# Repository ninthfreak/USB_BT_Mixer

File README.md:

# USB_BT_Mixer

A small box with two USB-C inputs and one Bluetooth audio output. Any USB-C host that supports USB audio sees each input as a normal USB sound card. The box mixes both inputs and streams the mix to any Bluetooth audio sink.

- **Architecture (start here): [`docs/architecture.md`](docs/architecture.md)**
- Decision log: [`docs/decisions.md`](docs/decisions.md)
- Design record: [`docs/HANDOFF.md`](docs/HANDOFF.md)
- Corrections since the handoff: [`docs/review-notes.md`](docs/review-notes.md)
- Design envelope (limits and extension points): [`docs/design-envelope.md`](docs/design-envelope.md)
- Viability review: [`docs/viability-review.md`](docs/viability-review.md)
- Parts list: [`hardware/BOM.csv`](hardware/BOM.csv)
- **Latest review (2026-11-16): [`docs/project-review-2026-11.md`](docs/project-review-2026-11.md)**

**Status (2026-11-16): designed, nothing built.**

| Part | State |
|---|---|
| Hardware | Two Waveshare RP2350-USB-C input boards and a Waveshare ESP32-DEV-KIT-WROOM-32E-N4 solder flat onto a carrier PCB ([`hardware/carrier/`](hardware/carrier/)). Routed and DRC clean; **not ordered**. Print [`carrier-fit-check.pdf`](hardware/carrier/carrier-fit-check.pdf) and lay the real boards on it first |
| Firmware | Not started. Design: [`docs/architecture.md`](docs/architecture.md) |
| Enclosure | The modelled box is for the earlier hand-wired build and is out of date. The carrier needs a new one |

Each input board's native USB port faces its host through the enclosure wall and reaches the shared rail through its own Schottky. The ESP32 mixes, owns the audio clock and is the Bluetooth A2DP source. Configured from any browser via a page the box serves over USB; no case buttons. See [`docs/decisions.md`](docs/decisions.md).

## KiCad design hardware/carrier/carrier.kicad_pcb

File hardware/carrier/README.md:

# Carrier board

> **Status: KiCad DRC clean, routed, not built, not ordered.**
>
> - **Re-laid 2026-11-16.** The input boards' land pattern had been the
>   mirror image of the real board since it was first drawn. It is corrected,
>   and the build now holds the placed board against Waveshare's own pictures
>   ([`docs/project-review-2026-11.md`](../../docs/project-review-2026-11.md) #1).
> - **Before ordering, print [`carrier-fit-check.pdf`](carrier-fit-check.pdf)
>   at 100 % and lay the three real modules on it.** Every land is named; the
>   names must match the labels on the modules.
> - **Antenna clearance: accepted as is** (owner, 2026-10-26). Copper is
>   6.55 mm in front of the antenna against Espressif's 15 mm; the antenna
>   itself hangs fully past the board edge
>   ([`AUDIT.md` #21](AUDIT.md#21-antenna-clearance-on-the-front-side-new)).
> - Recommendation before ordering: **the two-I2S clock loop-back is still
>   untested.** A jumper-wire bench test of one input board + the ESP32 would
>   prove it for the price of an afternoon.

One flat PCB that the three modules solder onto, replacing the hand-wired
loom. All passives are through-hole and live on it.

## At a glance

| | |
|---|---|
| Size | 70.0 × 79.6 mm, L-shaped (see below), 2 layers, 1.6 mm |
| Parts | U1, U2 input boards; U3 ESP32 devkit; 2 Schottky diodes; 8 resistors, all 1 kΩ (R1–R6 standing, R10/R11 lying); 1 capacitor; two 2-pin debug headers; 2 test pads |
| Nets | 20: 16 signal, 3 power (VBUS1, VBUS2, RAIL), GND |
| Rules | 0.40 mm track, 0.25 mm clearance, 0.8/0.4 mm vias, 0.5 mm copper to edge, 0.5 mm drill to drill. Loose for any fab |
| Top layer | **Every signal.** No signal changes layer: 0 signal vias |
| Bottom layer | Ground plane (91 % of the board) plus the rail only |
| Routing | Freerouting: 81 signal segments; the rail, ground stubs and three short links by hand; 568 mm of track; 5 vias, all ground |
| Joints to solder | 36 of 70 module lands, plus the passives |

## How the board is laid out

The rules, so it reads the way it works (owner, 2026-10-27):

- **Top layer: signals.** Every signal stays on top from end to end.
- **Bottom layer: ground and power.** A solid ground plane. The rail is the
  only track on it: from input 2's diode across the front, **in front of
  input 1's ground pad**, then down the left edge to the ESP32's 5V pad. No
  signal runs along it, and every module's ground via lands in the one main
  plane (review #2).
- **Related lines run together.** Each board's I2S lines and its UART pair
  travel as groups.

Each module lies exactly as in its picture in `docs/sources/`:

| Module | As placed | Picture |
|---|---|---|
| Input boards | **Native USB port at the front**, hanging 1 mm past the edge. 5V is the front-left pad. Power and I2S run down the **left** edge, UART and debug down the **right**. The PIO-USB port faces inward, unused | `rp2350-usb-c-pinout.png` |
| ESP32 | USB-C end 1 mm past the **left** edge, antenna past the notch on the **right**. The row facing the input boards is J3: 5V at the left … 3V3 at the antenna end | `esp32-dev-kit-drawing.png` |

Seen from the ESP32's front row, west to east:

| ESP32 pin | Carries | Goes to |
|---|---|---|
| IO13 | Input 1 audio | Down the left margin from input 1's left edge |
| IO14, IO26 | LRCK out, BCLK out, through R3 and R1 | Under input 1 to its left edge |
| IO25, IO33 | Input 1's UART (TX through R5, RX) | Up the channel to input 1's right edge |
| IO32, IO35 | BCLK in, LRCK in (the loop-backs), and on through R2 and R4 | To input 2's left edge |
| gaps east of IO35 | Input 2's audio, TX, and RX (through R6) | Under the ESP32 to IO18, IO19, IO21 on its rear row |

The clocks' output pins face input 1 and their loop-back pins face input 2,
so the two links under the ESP32 **nest instead of crossing**, and input 1's
UART ends on the two pads between them. Three lines pass between the pads of
a standing resistor (BCLK to input 1 under R3; input 2's audio under R2 and
R4). That is the only "crossing" on the board, and it is why no signal needs
the bottom layer.

| Where | What |
|---|---|
| Left margin | Input 1's diode D1 and bleed R10 at its 5V pad; the rail (bottom); test points; rail bulk C1 at the ESP32's 5V pad |
| Channel between the boards | Input 2's diode D2 and bleed R11 at its 5V pad; input 1's debug header J1; input 1's UART lanes |
| Strip in front of the ESP32 | R3, R1, R5, R2, R4, R6 standing in a row, each at the pin or gap it serves |
| Right margin | Input 2's debug header J2 |

## Why it is an L, not a rectangle

The front must be 70 mm wide for the two input boards side by side. The ESP32
devkit sits across the back, its USB-C end hanging 1 mm past the left edge so
a flashing cable fits. That puts the antenna at the right.

Espressif's first choice is an antenna **outside** the base board, with any
board under it cut away. So the back-right corner is cut off and the
devkit's antenna end hangs 7.5 mm into free air. An L costs nothing extra:
fabs price by the bounding box.

The catch is the antenna's front side, where the front-right block comes
close: 6.55 mm, where Espressif asks for 15. The owner accepted that rather
than make the board ~8.5 mm deeper ([AUDIT.md #21](AUDIT.md#21-antenna-clearance-on-the-front-side-new)).

## Build

```sh
./build.sh                          # regenerate and check everything
/usr/bin/python3 route.py --reroute # only after moving parts or changing nets
```

Everything runs under the **system** python (`/usr/bin/python3`), which has
KiCad 7's `pcbnew` bindings. Every step must pass.

The build does **not** run Freerouting: its output varies from run to run.
It lays the committed result, `carrier.ses`. If the placement or netlist has
changed since that route was made, `route.py` stops and says to reroute.
Rerouting downloads Freerouting 2.1.0 once (SHA-256 checked, analytics off)
and needs Java 17 or later; it takes a few seconds. Whether a route is
complete is decided by KiCad's connectivity, not by Freerouting's own count.

`carrier.kicad_sch`, `carrier.kicad_pcb`, `carrier.pretty/`,
`CONNECTIONS.md` and the PDFs are generated. Edit `netlist.py` (connectivity),
`gen_pcb.py` (placement) or `route.py` (hand-laid copper) and rebuild. Never
hand-edit the outputs.

## Files

| File | What |
|---|---|
| `netlist.py` | **Single source of truth** for connectivity: parts, pin maps, nets, footprints, and what is deliberately unconnected |
| `gen_fp.py` | The two module land patterns, from `enclosure/boards.scad`, each drawn as its picture |
| `gen_sch.py` | `carrier.kicad_sch` |
| `gen_table.py` | `CONNECTIONS.md`: every net, and which pads to solder |
| `gen_pcb.py` | `carrier.kicad_pcb`, built with pcbnew: outline, placement, pad nets, schematic links, labels, the ground pour |
| `route.py` | Lays the rail, ground stubs and three links by hand, every other signal from `carrier.ses`; `--reroute` runs Freerouting to make a new one |
| `specctra.py` | Design export edits and session import between KiCad and Freerouting |
| `carrier.ses`, `carrier-route.json` | The committed route, and the hash of the design it was made for |
| `drc.py` | **The gate.** KiCad's own DRC with this board's rules, plus every pad's net against `netlist.py` |
| `check_footprints.py` | Recomputes every pad coordinate from `boards.scad` |
| `check_netlist.py` | Reads the netlist back out of the schematic and diffs it; checks diode and capacitor polarity against the footprint's own markings |
| `check_pcb.py` | **Each module lies as in its picture, not mirrored**; native USB ports over the front edge; ESP32 overhangs at both ends; hole webs |
| `check_routing.py` | Routed intent: power widths, I2S chain lengths, bottom pour coverage, every signal on top, and a ground path at least 2 mm wide from each input board to the ESP32 |
| `fit_check.py` | `carrier-fit-check.pdf`: the board at 1:1 with every module pad named, to print and lay the real modules on. Also the soldering map |
| `AUDIT.md` | The 2026-10-26 audit and what was done about each finding |

## How it is verified

KiCad's DRC (`pcbnew.WriteDRCReport`) is the authority: clearances,
connectivity including the pour, courtyards, holes, silkscreen, keep-outs.

The custom checks cover what DRC cannot know: design intent. Each one has
been shown to **fail** on a deliberately broken board, not only to pass:

| Break | Caught by | Result |
|---|---|---|
| Input boards' pattern mirrored (pads 1–9 on the right: **the bug this board had**) | `check_pcb.py` | every corner pad listed: "the picture has it west/front, the board has it east/front" |
| Input 1 turned half a turn | `check_pcb.py` | corners listed; no proud shell at the front |
| ESP32's two rows swapped | `check_pcb.py` | 5V, IO36, CLK, IO22 listed |
| Diode pins mapped A=1 (the 2026-10 bug) | `check_netlist.py` | polarity failures |
| Delete a track | `drc.py` | unconnected, dangling |
| Empty the GND pour | `drc.py` | many unconnected |
| Track 0.3 mm from the edge | `drc.py` | edge clearance |
| Power traces at 0.4 mm | `check_routing.py` | every thin segment listed |
| A signal track on the bottom, a via on a signal | `check_routing.py` | both listed |
| Rail run behind the input boards' ground pads (DRC still clean, 89 % fill) | `check_routing.py` | ground path narrower than 2 mm, all four pairs listed |
| ESP32 USB-C end flush (no overhang) | `check_pcb.py` | fails |
| Antenna overhang 3 mm | `check_pcb.py` | fails |
| R10 moved 1 mm, old route laid | `route.py` | refuses: "routed for a different placement" |

**What no check here can do** is confirm the pictures match the boards in
your hand. That is what the paper fit check is for.

One KiCad behaviour worth knowing when testing: saving a board reassigns a
track that is not connected to its own net to whatever copper it touches (in
practice, the ground pour). A test track must therefore join two pads of its
net. DRC still catches the missing connection a reassigned track leaves.

`drc-report.txt` holds the last report. Its only entries are
"library not in this configuration" notes: the container has no global KiCad
library table. They say nothing about the copper.

## Pin numbering

We draw both the symbol and the footprint, so the numbering is ours. Each is
defined against a picture, because "left" means nothing without one.

**RP2350-USB-C** — `docs/sources/rp2350-usb-c-pinout.png`: component side
up, native USB port (beside BOOT and RST) at the top:

- pads 1–9, **left** edge top to bottom: `5V GND 3V3 GP29 GP28 GP27 GP26 GP10 GP9`
- pads 10–18, **right** edge top to bottom: `GP0 GP1 GP2 GP3 GP4 GP5 GP6 GP7 GP8`

**ESP32-DEV-KIT** — `docs/sources/esp32-dev-kit-drawing.png`: component side
up, USB-C left, antenna right:

- pads 1–19 are header J3, the **top** row, numbered from the antenna end:
  pad 1 = 3V3 (right) … pad 19 = 5V (left)
- pads 20–38 are J4, the **bottom** row, also from the antenna end (so J4 pin
  *n* is our pad 19 + *n*): pad 20 = GND … pad 38 = CLK
- pads 1, 2, 20 and 21 have no land: they sit past the notch.

## Land patterns

Both modules are castellated, so they solder flat with the iron on the
**outside** of every joint: visible, inspectable, reworkable, no reflow.

Each pad is 1.30 mm along the edge × 3.00 mm across, sticking out 1.10 mm past
the module outline. At 2.54 mm pitch that leaves 1.24 mm between pads. The
pads reference the board **outline**, so the ESP32's header row spacing never
enters the footprint.

Each footprint is drawn as its picture looks in KiCad's footprint editor,
where +Y points **down**:

| Footprint | Drawn | Placed |
|---|---|---|
| `RP2350-USB-C` | Native USB port at the top (−Y), 5V top-left | Unrotated |
| `ESP32-DEV-KIT` | The drawing turned half a turn: antenna left (−X), J3 at the bottom (+Y) | Turned 180°, which makes it the drawing again |

Passives use stock KiCad footprints: DO-41 diodes and the two bleed resistors
at 7.62 mm, the six series resistors standing at 2.54 mm, the bulk cap radial
at 2.50 mm.

## Dimensions: use what is recorded

Both modules are dimensioned by Waveshare drawings, already written down in
`enclosure/boards.scad`, with the pictures in `docs/sources/`. **Do not ask
the owner to re-measure them.** Both modules are flat underneath (owner,
boards in hand).

## Soldering: not every pad

Solder only the pads that carry a net, plus a few corners so nothing can peel.
**36 joints instead of 70.** `CONNECTIONS.md` has the per-pad map and
`carrier-fit-check.pdf` shows it at 1:1. `check_netlist.py` asserts every
mechanical pad floats; several are the ESP32's flash and strapping pins, and
tying those to live copper would be worse than leaving them bare.

Suggested order: the three modules first, while the board lies flat and
every pad is easy to reach; then the through-hole parts, soldered from
underneath.

The full land pattern is still made, so any pad can be soldered later.

### Plug forces

Each input board's first pads are 2.88 mm from its native USB-C shell, and
the soldered 5V, GND and GP0 joints sit at that end. They take some of a
cable's peel moment, but solder is still the wrong thing to rely on: whatever
enclosure holds the carrier should bear on the modules near the port.

## Programming with everything soldered

- **Input boards:** through the front USB-C port (native USB). First flash:
  hold BOOT while plugging in and copy the UF2. BOOT is on the board's top
  face, beside that port (Waveshare's picture). After that, firmware can
  reboot into its bootloader on command.
- **ESP32:** through its own USB-C, hanging past the left edge; no buttons
  needed, and the box can stay powered.

Details: `hardware/wiring.md`, "Programming with everything soldered".

## Deliberate design choices

- **The two 3V3 rails are never tied together.** Each module has its own
  regulator. Asserted in `NO_CONNECT`.
- **Each input board reaches the rail only through its own Schottky**, so the
  two hosts' 5 V supplies never meet.
- **A 1 kΩ bleed on each input board's VBUS** (R10, R11). An input board with
  no host is fed its diode's reverse leakage from the rail; a USB-C host will
  not switch a port on until VBUS is below 0.8 V.
- **The clocks go to GP9 and GP10, the UART to GP5**: fault-tolerant pads,
  which pass almost no current when their board is unpowered. GP26–GP29 (the
  ADC pads, which have a diode to that board's 3V3 rail) take no signal from
  the ESP32.
- **1 kΩ in series with every line the ESP32 drives into an input board**
  (BCLK, LRCK, UART TX): edge-rate control beside the radio, and a limit if a
  pin is ever turned the wrong way round.
- **Never IO36/IO39** for I2S: they glitch when the ADC powers up (Espressif
  erratum; reported during A2DP streaming). The loop-backs are IO26→IO32 and
  IO14→IO35.
- **Both audio inputs (IO13, IO18) have an internal pull-down** for firmware
  to switch on, so a board with no host contributes silence.
- **TP1/TP2** (rail and ground, 3 mm apart in the left margin) because the
  rail voltage is an estimate that must be measured on the built box
  (review-notes #18).

Retired 2026-11-16 as not needed (review #5): R7 (AUD2 pull-down), R8/R9
(GP29 pull-downs), C2–C4 (0.1 µF bypasses). The designators are not reused.

## Still open

| Item | State |
|---|---|
| **Paper fit check** | **Not done.** Print `carrier-fit-check.pdf` at 100 %; the names must match the modules' own labels |
| Antenna clearance, front side | **Accepted as is** (owner). If Bluetooth range disappoints, option C in [AUDIT.md #21](AUDIT.md#21-antenna-clearance-on-the-front-side-new) is the fix |
| I2S loop-back and UART relay | **Untested** in hardware. Bench test before ordering (recommended) |
| Bleed and back-feed | Two five-minute multimeter tests settle them (review #3, #4) |
| Enclosure for the carrier | Not designed. Its port wall must take the native port's **proud** shell; the left wall needs an opening (or a removable plug) at the ESP32's USB-C; the carrier needs standoffs because through-hole leads protrude underneath; C1 and the standing resistors set the height |
| Native-USB shell overhang | 1.00 mm assumed (`usb_over_in`); worth a caliper check before the enclosure |
| ESP32 sources | The dimensioned drawing is archived. The schematic PDF is still not in the repo. Not a blocker |

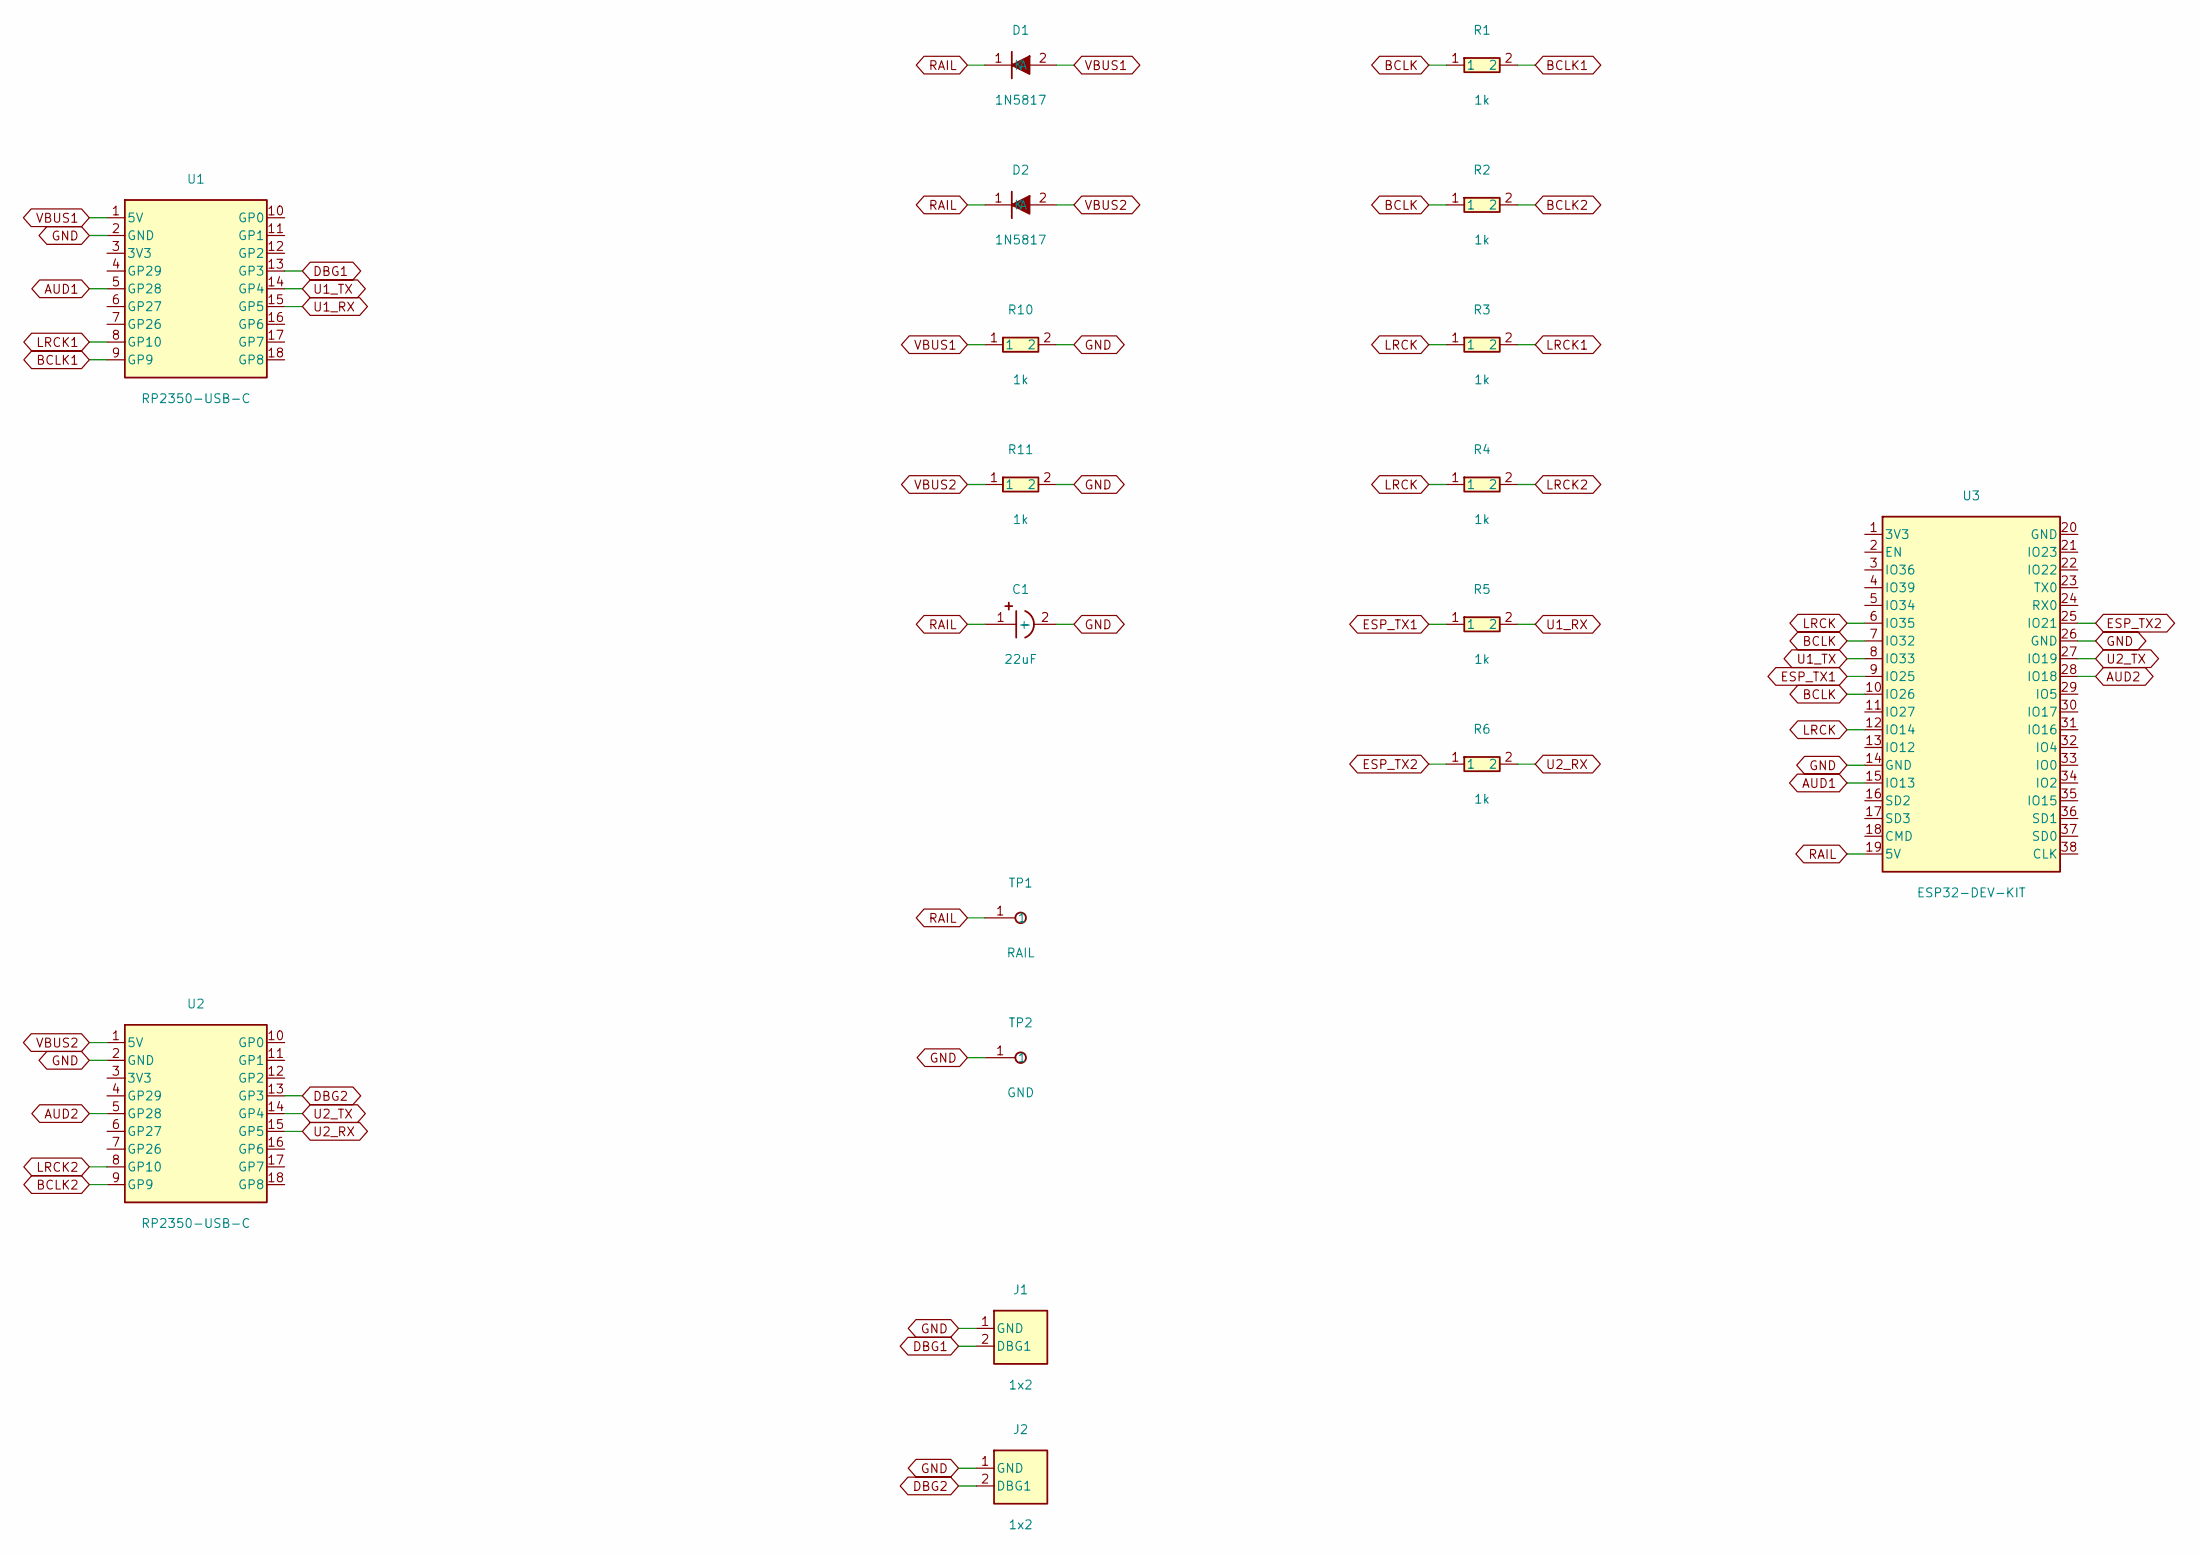
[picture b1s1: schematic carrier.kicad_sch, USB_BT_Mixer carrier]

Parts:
C1: 22uF; CP_Radial_D5.0mm_P2.50mm
D1, D2: 1N5817; D_DO-41_SOD81_P7.62mm_Horizontal
J1, J2: 1x2; PinHeader_1x02_P2.54mm_Vertical
R1, R2, R3, R4, R5, R6: 1k; R_Axial_DIN0207_L6.3mm_D2.5mm_P2.54mm_Vertical
R10, R11: 1k; R_Axial_DIN0207_L6.3mm_D2.5mm_P7.62mm_Horizontal
TP1: RAIL; TestPoint_Pad_D1.5mm
TP2: GND; TestPoint_Pad_D1.5mm
U1, U2: RP2350-USB-C
U3: ESP32-DEV-KIT

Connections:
AUD1: U1.5 (GP28), U3.15 (IO13)
AUD2: U2.5 (GP28), U3.28 (IO18)
BCLK: R1.1, R2.1, U3.7 (IO32), U3.10 (IO26)
BCLK1: R1.2, U1.9 (GP9)
BCLK2: R2.2, U2.9 (GP9)
DBG1: J1.2 (DBG1), U1.13 (GP3)
DBG2: J2.2 (DBG1), U2.13 (GP3)
ESP_TX1: R5.1, U3.9 (IO25)
ESP_TX2: R6.1, U3.25 (IO21)
GND: C1.2 (-), J1.1 (GND), J2.1 (GND), R10.2, R11.2, TP2.1, U1.2 (GND), U2.2 (GND), U3.14 (GND), U3.26 (GND)
LRCK: R3.1, R4.1, U3.6 (IO35), U3.12 (IO14)
LRCK1: R3.2, U1.8 (GP10)
LRCK2: R4.2, U2.8 (GP10)
RAIL: C1.1 (+), D1.1 (K), D2.1 (K), TP1.1, U3.19 (5V)
U1_RX: R5.2, U1.15 (GP5)
U1_TX: U1.14 (GP4), U3.8 (IO33)
U2_RX: R6.2, U2.15 (GP5)
U2_TX: U2.14 (GP4), U3.27 (IO19)
VBUS1: D1.2 (A), R10.1, U1.1 (5V)
VBUS2: D2.2 (A), R11.1, U2.1 (5V)

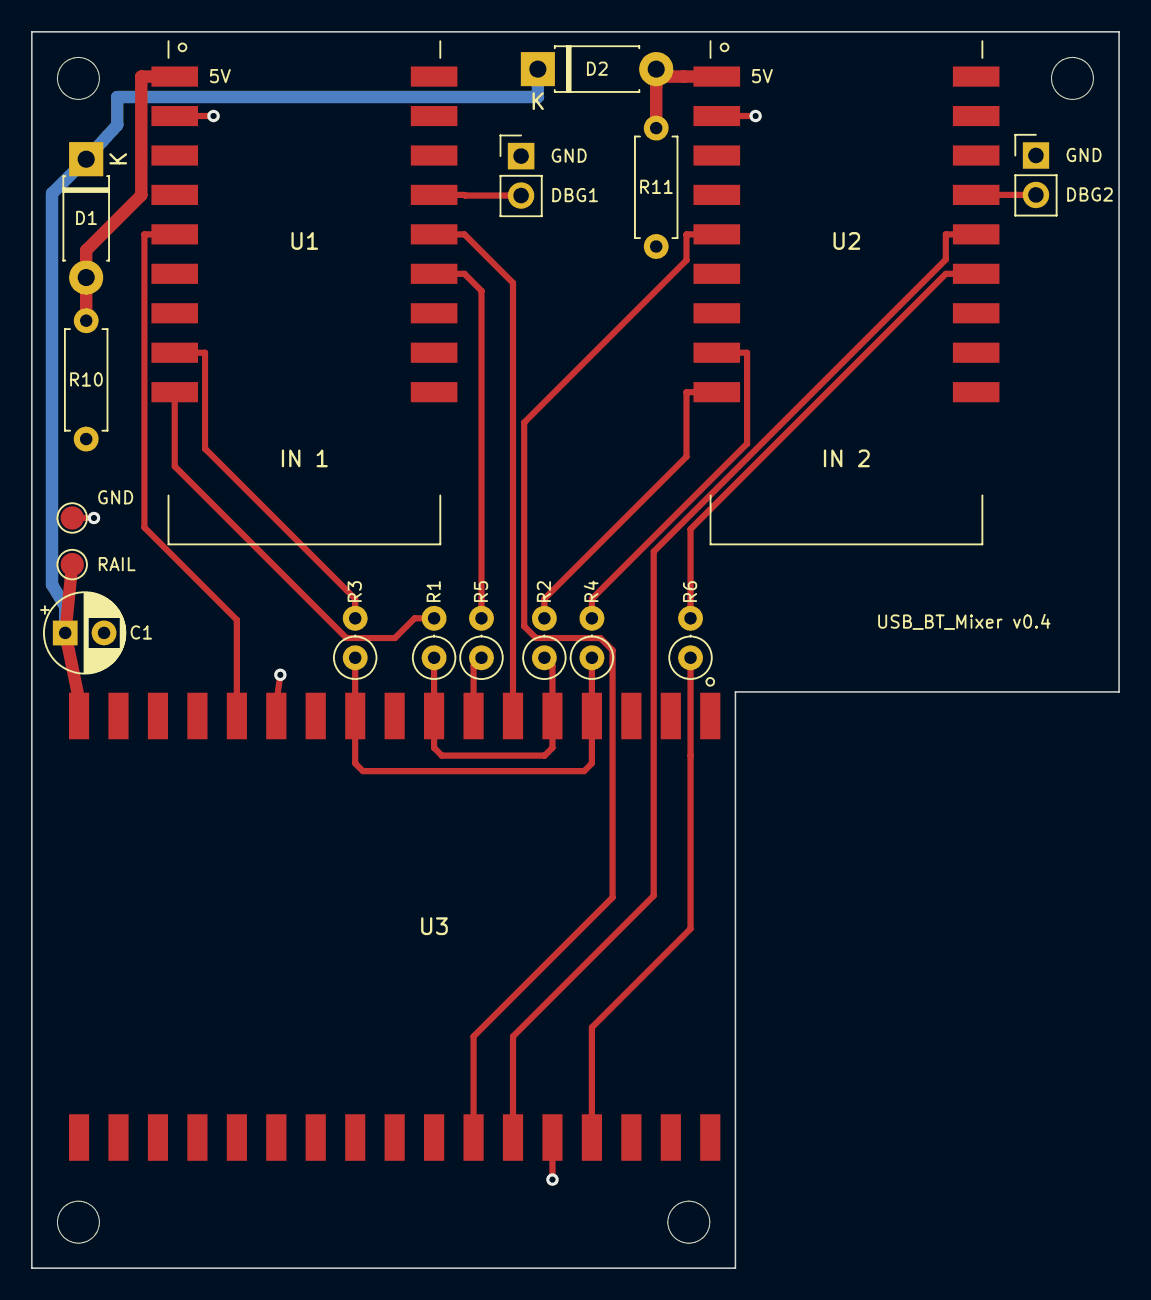
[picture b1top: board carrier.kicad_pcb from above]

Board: 2 copper layers, 70.0 x 79.6 mm, 22 parts (0 on the bottom side), 20 nets.

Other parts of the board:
H1, H2, H3, H4: MountingHole_2.7mm_M2.5

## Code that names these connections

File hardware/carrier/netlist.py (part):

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    # One 2-pin header beside each input board's GP3, not one shared 3-pin:
    # a shared header meant a debug line crossing under input 2.
    "J1": dict(kind="hdr", value="1x2", desc="Input 1 debug serial (optional)",
               pins=["GND", "DBG1"]),
    "J2": dict(kind="hdr", value="1x2", desc="Input 2 debug serial (optional)",
               pins=["GND", "DBG2"]),
    "TP1": dict(kind="tp", value="RAIL", desc="Rail test point -- MEASURE here"),
    "TP2": dict(kind="tp", value="GND", desc="Ground test point"),
}
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    # On the input boards the clocks go to GP9 and GP10, not GP26/GP27. Only
    # GP26-GP29 are ADC-capable, and those four are the pads with a diode to
    # the board's 3V3 rail; a clock driven into one while that board has no
    # host would power its rail through the pin. GP9/GP10 are consecutive
    # (one PIO "in" group) and sit next along the same edge.
    #
    # The ESP32 pins are chosen for the PCB layout. Along its front row,
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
